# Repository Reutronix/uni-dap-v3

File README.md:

# UniDAP

**Galvanically isolated CMSIS-DAP debug probe with USB-to-I²C/SPI/GPIO bridging.**

UniDAP is an open hardware debug/programming probe. It combines a full USB-isolated CMSIS-DAP probe (SWD + UART) with a USB-to-I²C/SPI/GPIO bridge, so a single USB-C cable gives you target programming, a serial console, general-purpose bus access, and isolated power — all on the far side of a galvanic isolation barrier.

---

## Features

- **Full galvanic isolation** between the host USB and the target — data *and* power.
- **CMSIS-DAP / DAPLink probe** on an STM32F103 (SWD + virtual UART).
- **USB-to-I²C/SPI/GPIO bridge** via a WCH CH347F, exposed on the same output header.
- **Isolated power rails** to the target: 5 V, 3.3 V, and a **software-gated** power output.
- **Two SWD interfaces**: a 2.54 mm 24-position fan-out header and a standard 1.27 mm 10-pin ARM Cortex Debug box header.
- **Optional UART level shifter** referenced to the target supply.
- **Self-programmable**: the on-board STM32 can be flashed for the first time over the CH347, with no external tools.

---

## Architecture

A single USB-C connection is isolated for both data and power, then fanned out on the isolated side to the STM32 (DAPLink) and the CH347 through a 2-port USB hub.

```mermaid
flowchart TB
    subgraph HOST["Host side (non-isolated)"]
        USBC["USB-C"]
    end

    subgraph BARRIER["Isolation barrier"]
        ADUM["ADuM4160<br/>USB isolator<br/>+ current limit / reverse-current protection"]
        SN["SN6505ADBV + transformer<br/>isolated 5 V supply"]
    end

    subgraph ISO["Isolated side"]
        HUB["CY7C65634<br/>2-port USB hub"]
        STM["STM32F103<br/>DAPLink (SWD + UART)"]
        CH["CH347F<br/>USB → I²C / SPI / GPIO"]
        H20["24-pin 2.54 mm<br/>output header"]
        H10["10-pin 1.27 mm<br/>Cortex Debug"]
    end

    USBC --> ADUM --> HUB
    USBC --> SN
    SN -. isolated 5 V .-> ISO
    HUB --> STM
    HUB --> CH
    STM -->|SWD + UART| H20
    STM -->|SWD| H10
    CH -->|I²C / SPI / GPIO| H20
```

### Key components

| Function | Part |
|---|---|
| Main MCU / debug probe | STM32F103 (running DAPLink) |
| USB → I²C / SPI / GPIO bridge | WCH CH347F |
| USB isolator | Analog Devices ADuM4160 |
| Isolated 5 V supply | TI SN6505ADBV push-pull transformer driver + transformer |
| USB hub (isolated side) | Cypress CY7C65634 (2-port) |
| Gated power output | ideal-diode switch, GPIO-controlled |
| UART level shifter (optional) | U502 (target-referenced) |

---

## Connectors & pinouts

### 24-pin 2.54 mm output header

The main fan-out header carries the SWD programming signals from the STM32, the DAPLink UART, the CH347 I²C/SPI/GPIO lines, and the isolated power rails (5 V, 3.3 V, and the gated `VOUT`). It uses an odd/even footprint: odd pins on one row, even pins on the other, with pin 1 and pin 2 side by side. Refer to on-board bottom side silkscreen.

| Pin | Signal | Group | | Pin | Signal | Group |
|----:|--------|-------|---|----:|--------|-------|
| 1 | GND | Ground | | 2 | 5V | Power |
| 3 | 3.3V | Power | | 4 | VOUT | Gated power |
| 5 | GPIO5 | GPIO | | 6 | GND | Ground |
| 7 | GND | Ground | | 8 | SCL | I²C |
| 9 | GPIO1 | GPIO | | 10 | SDA | I²C |
| 11 | SPI_SCK | SPI | | 12 | GPIO2 | GPIO |
| 13 | SPI_CS | SPI | | 14 | GND | Ground |
| 15 | SPI_MISO | SPI | | 16 | UART_TX | UART |
| 17 | SPI_MOSI | SPI | | 18 | UART_RX | UART |
| 19 | GPIO3 | GPIO | | 20 | GND | Ground |
| 21 | GND | Ground | | 22 | SWCLK | SWD |
| 23 | RESET | SWD | | 24 | SWDIO | SWD |

> **Note:** `VOUT` (pin 4) is the gated power output. In the standard configuration it is switched by CH347 **GPIO1** (pin 9) through the on-board ideal diode — see [Configuration](#configuration-jumpers--dnp-options). `RESET` (pin 23) is the target reset line.

### 10-pin 1.27 mm Cortex Debug header

Standard ARM Cortex Debug connector pinout — compatible with common SWD adapters and cables.

| Pin | Signal | Pin | Signal |
|----:|--------|----:|--------|
| 1 | VTREF | 2 | SWDIO / TMS |
| 3 | GND | 4 | SWCLK / TCK |
| 5 | GND | 6 | SWO / TDO |
| 7 | KEY (n/c) | 8 | NC / TDI |
| 9 | GNDDetect | 10 | nRESET |

### STM32 SWD programming pads (SMD)

Bare SMD pads are provided to program the STM32 over SWD directly (solder wires). Used mainly to recover a blank part or one without a USB bootloader. See [First-time STM32 programming](#first-time-stm32-programming).

---

## Configuration (jumpers & DNP options)

UniDAP ships in a **standard configuration**; several jumpers/footprints let you reconfigure it.

| Ref | Default | Function |
|---|---|---|
| **R501** | Populated | Routes CH347 **GPIO1** to the ideal-diode gate, so GPIO1 controls the **gated power output** (standard config). |
| **R502** | Unpopulated | Alternate route for CH347 GPIO1 to the main output header as a plain GPIO. **Populate R502 and remove R501** to expose GPIO1 on the header instead of driving the gated output. |
| **U502** | Unpopulated | Optional UART **level shifter**, supplied from the target voltage. |
| **R505 / R507** | Populated | Direct (unshifted) connection of the DAPLink UART to the output header. **Remove R505/R507 and populate U502** to route the UART through the level shifter. |

**Gated power output:** by default the isolated power to the target passes through an ideal-diode switch enabled by CH347 GPIO1, so power to the target can be switched under software control.

**Level-shifted UART:** in the standard configuration the DAPLink UART goes straight to the output header. Populating U502 (and removing R505/R507) shifts the UART to the target's logic level, referenced to the target supply.

---

## Firmware

The probe runs [DAPLink](https://github.com/ARMmbed/DAPLINK) (main branch).

- **Board ID:** `0080`
- **Provides:** CMSIS-DAP (SWD) + a virtual UART bridge.

### First-time STM32 programming

The STM32 can be programmed for the first time (or recovered when no USB bootloader is present) two ways:

1. **Over the CH347 (no external tools).** The CH347 UART0 is wired to the STM32 UART, and the STM32 **BOOT0** pin is driven by CH347 **GPIO0**. Asserting BOOT0 enters the STM32F103 system bootloader, and the firmware is flashed over UART. Use STM32CubeProgrammer to download the image.
2. **Over SWD.** Solder wires to the SWD SMD pads and flash with any CMSIS-DAP/ST-Link adapter.

---

## Acknowledgements

- [DAPLink](https://github.com/ARMmbed/DAPLINK) by Arm — the CMSIS-DAP firmware UniDAP is based on.
- WCH (CH347), Analog Devices (ADuM4160), TI (SN6505), Cypress/Infineon (CY7C65634).

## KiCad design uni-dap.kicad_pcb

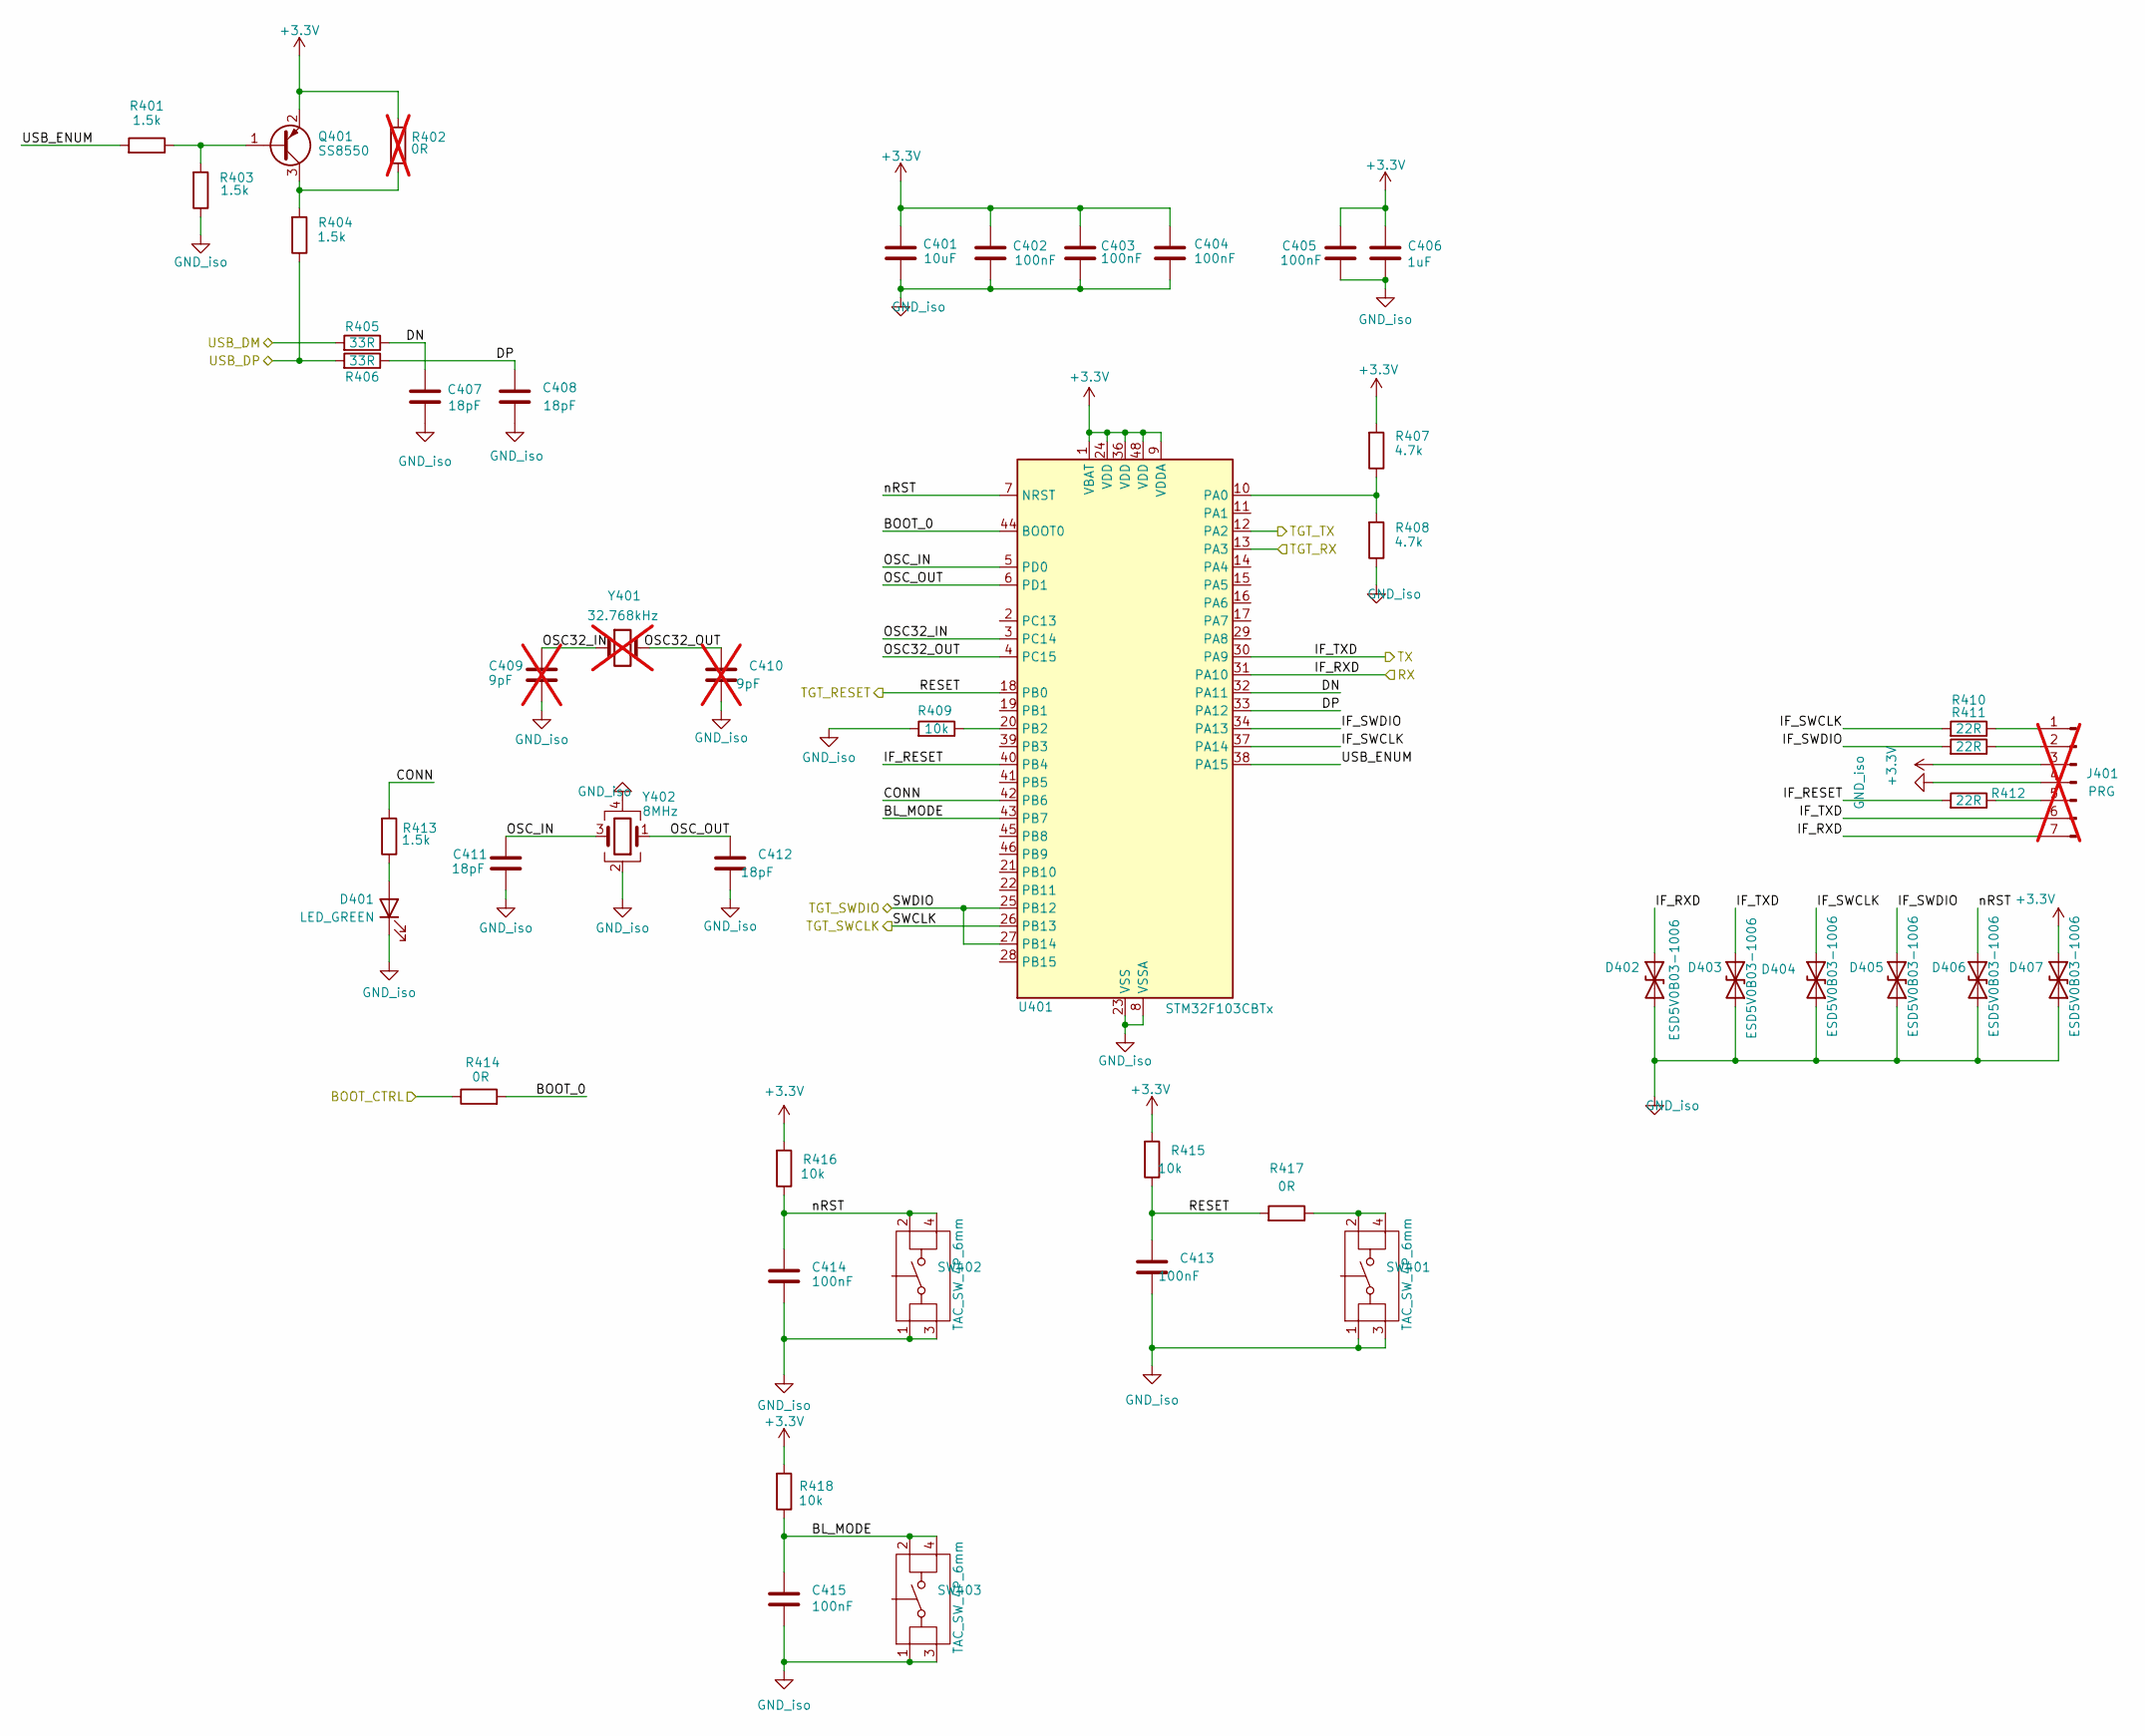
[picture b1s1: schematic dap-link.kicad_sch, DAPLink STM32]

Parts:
C401: 10uF; C_0603; Voltage 16; Manuf PN CL10A106MO8NQNC; LCSC PN C92487
C402, C403, C404, C405, C413, C414, C415: 100nF; C_0402; Voltage 16V; Manuf PN CL05B104KO5NNNC; LCSC PN C1525
C406: 1uF; C_0402; Voltage 16V; Manuf PN CL05A105KO5NNNC; LCSC PN C29266
C407, C408, C411, C412: 18pF; C_0402; Voltage 50V; Manuf PN CC0402JRNPO9BN180; LCSC PN C106202
C409, C410: 9pF; C_0402; Voltage 50V; Manuf PN CL05C090DB5NNNC; LCSC PN C111805; not fitted
D401: LED_GREEN; LED_0402; Manuf PN 16-213/GHC-YR1S1N/3T; LCSC PN C2980183
D402, D403, D404, D405, D406, D407: ESD5V0B03-1006; DFN1006-2_SMD0402; Clamping Voltage 21V; Manuf PN ESD5V0B03-1006; LCSC PN C521894
J401: PRG; PROG_HEADER_SMD; not fitted
Q401: SS8550; SOT-323_SC-70; Manuf PN SS8550WGH; LCSC PN C47355426
R401, R403, R404, R413: 1.5k; R_0402; Manuf PN RC0402FR-071K5L; LCSC PN C114759
R402: 0R; R_0402; Manuf PN RC0402FR-070RL; LCSC PN C106231; not fitted
R405, R406: 33R; R_0402; Manuf PN RC0402FR-0733RL; LCSC PN C138002
R407, R408: 4.7k; R_0402; Manuf PN RC0402FR-074K7L; LCSC PN C105871
R409, R415, R416, R418: 10k; R_0402; Manuf PN RC0402FR-0710KL; LCSC PN C60490
R410, R411, R412: 22R; R_0402; Manuf PN RC0402FR-0722RL; LCSC PN C114765
R414, R417: 0R; R_0402; Manuf PN RC0402FR-070RL; LCSC PN C106231
SW401, SW402, SW403: TAC_SW_4P_6mm; TS_6x6mm; Manuf PN TS-1002S-07026C; LCSC PN C455114
U401: STM32F103CBTx; LQFP-48_7x7mm_P0.5mm
Y401: 32.768kHz; Crystal_SMD_3215-2Pin_3.2x1.5mm; Manuf PN 9HT10-32.768KBZC-T; LCSC PN C99010; not fitted
Y402: 8MHz; Crystal_SMD_2520-4Pin_2.5x2.0mm; Manuf PN XOS25008000LT00351005; LCSC PN C37635403

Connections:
+3.3V: C401.2, C402.1, C403.1, C404.1, C405.1, C406.1, D407.2 (A2), J401.3, Q401.2 (E), R402.1, R407.1, R415.1, R416.1, R418.1, U401.1 (VBAT), U401.9 (VDDA), U401.24 (VDD), U401.36 (VDD), U401.48 (VDD); also elsewhere on the board
/DAPLink/BL_MODE: C415.1, R418.2, SW403.2 (B), SW403.4 (B), U401.43 (PB7)
/DAPLink/BOOT_0: R414.1, U401.44 (BOOT0)
/DAPLink/BOOT_CTRL: R414.2; also elsewhere on the board
/DAPLink/CONN: R413.1, U401.42 (PB6)
/DAPLink/DN: C407.1, R405.2, U401.32 (PA11)
/DAPLink/DP: C408.1, R406.2, U401.33 (PA12)
/DAPLink/IF_RESET: R412.1, U401.40 (PB4)
/DAPLink/IF_RXD: D402.2 (A2), J401.7, U401.31 (PA10); also elsewhere on the board
/DAPLink/IF_SWCLK: D404.2 (A2), R410.1, U401.37 (PA14)
/DAPLink/IF_SWDIO: D405.2 (A2), R411.1, U401.34 (PA13)
/DAPLink/IF_TXD: D403.2 (A2), J401.6, U401.30 (PA9); also elsewhere on the board
/DAPLink/OSC32_IN: C409.1, U401.3 (PC14), Y401.1
/DAPLink/OSC32_OUT: C410.1, U401.4 (PC15), Y401.2
/DAPLink/OSC_IN: C411.1, U401.5 (PD0), Y402.3
/DAPLink/OSC_OUT: C412.1, U401.6 (PD1), Y402.1
/DAPLink/RESET: C413.1, R415.2, R417.1, U401.18 (PB0); also elsewhere on the board
/DAPLink/SWCLK: U401.26 (PB13); also elsewhere on the board
/DAPLink/SWDIO: U401.25 (PB12), U401.27 (PB14); also elsewhere on the board
/DAPLink/TGT_RX: U401.13 (PA3); also elsewhere on the board
/DAPLink/TGT_TX: U401.12 (PA2); also elsewhere on the board
/DAPLink/USB_ENUM: R401.1, U401.38 (PA15)
/DAPLink/nRST: C414.1, D406.2 (A2), R416.2, SW402.2 (B), SW402.4 (B), U401.7 (NRST)
/USB/USB1_N: R405.1; also elsewhere on the board
/USB/USB1_P: R404.2, R406.1; also elsewhere on the board
GND_iso: C401.1, C402.2, C403.2, C404.2, C405.2, C406.2, C407.2, C408.2, C409.2, C410.2, C411.2, C412.2, C413.2, C414.2, C415.2, D401.1 (K), D402.1 (A1), D403.1 (A1), D404.1 (A1), D405.1 (A1), D406.1 (A1), D407.1 (A1), J401.4, R403.2, R408.2, R409.1, SW401.1 (A), SW401.3 (A), SW402.1 (A), SW402.3 (A), SW403.1 (A), SW403.3 (A), U401.8 (VSSA), U401.23 (VSS), U401.35 (VSS), U401.47 (VSS), Y402.2, Y402.4; also elsewhere on the board
unnamed: D401.2 (A), R413.2
unnamed: J401.1, R410.2
unnamed: J401.2, R411.2
unnamed: J401.5, R412.2
unnamed: Q401.1 (B), R401.2, R403.1
unnamed: Q401.3 (C), R402.2, R404.1
unnamed: R417.2, SW401.2 (B), SW401.4 (B)
unnamed: R407.2, R408.1, U401.10 (PA0)
unnamed: R409.2, U401.20 (PB2)

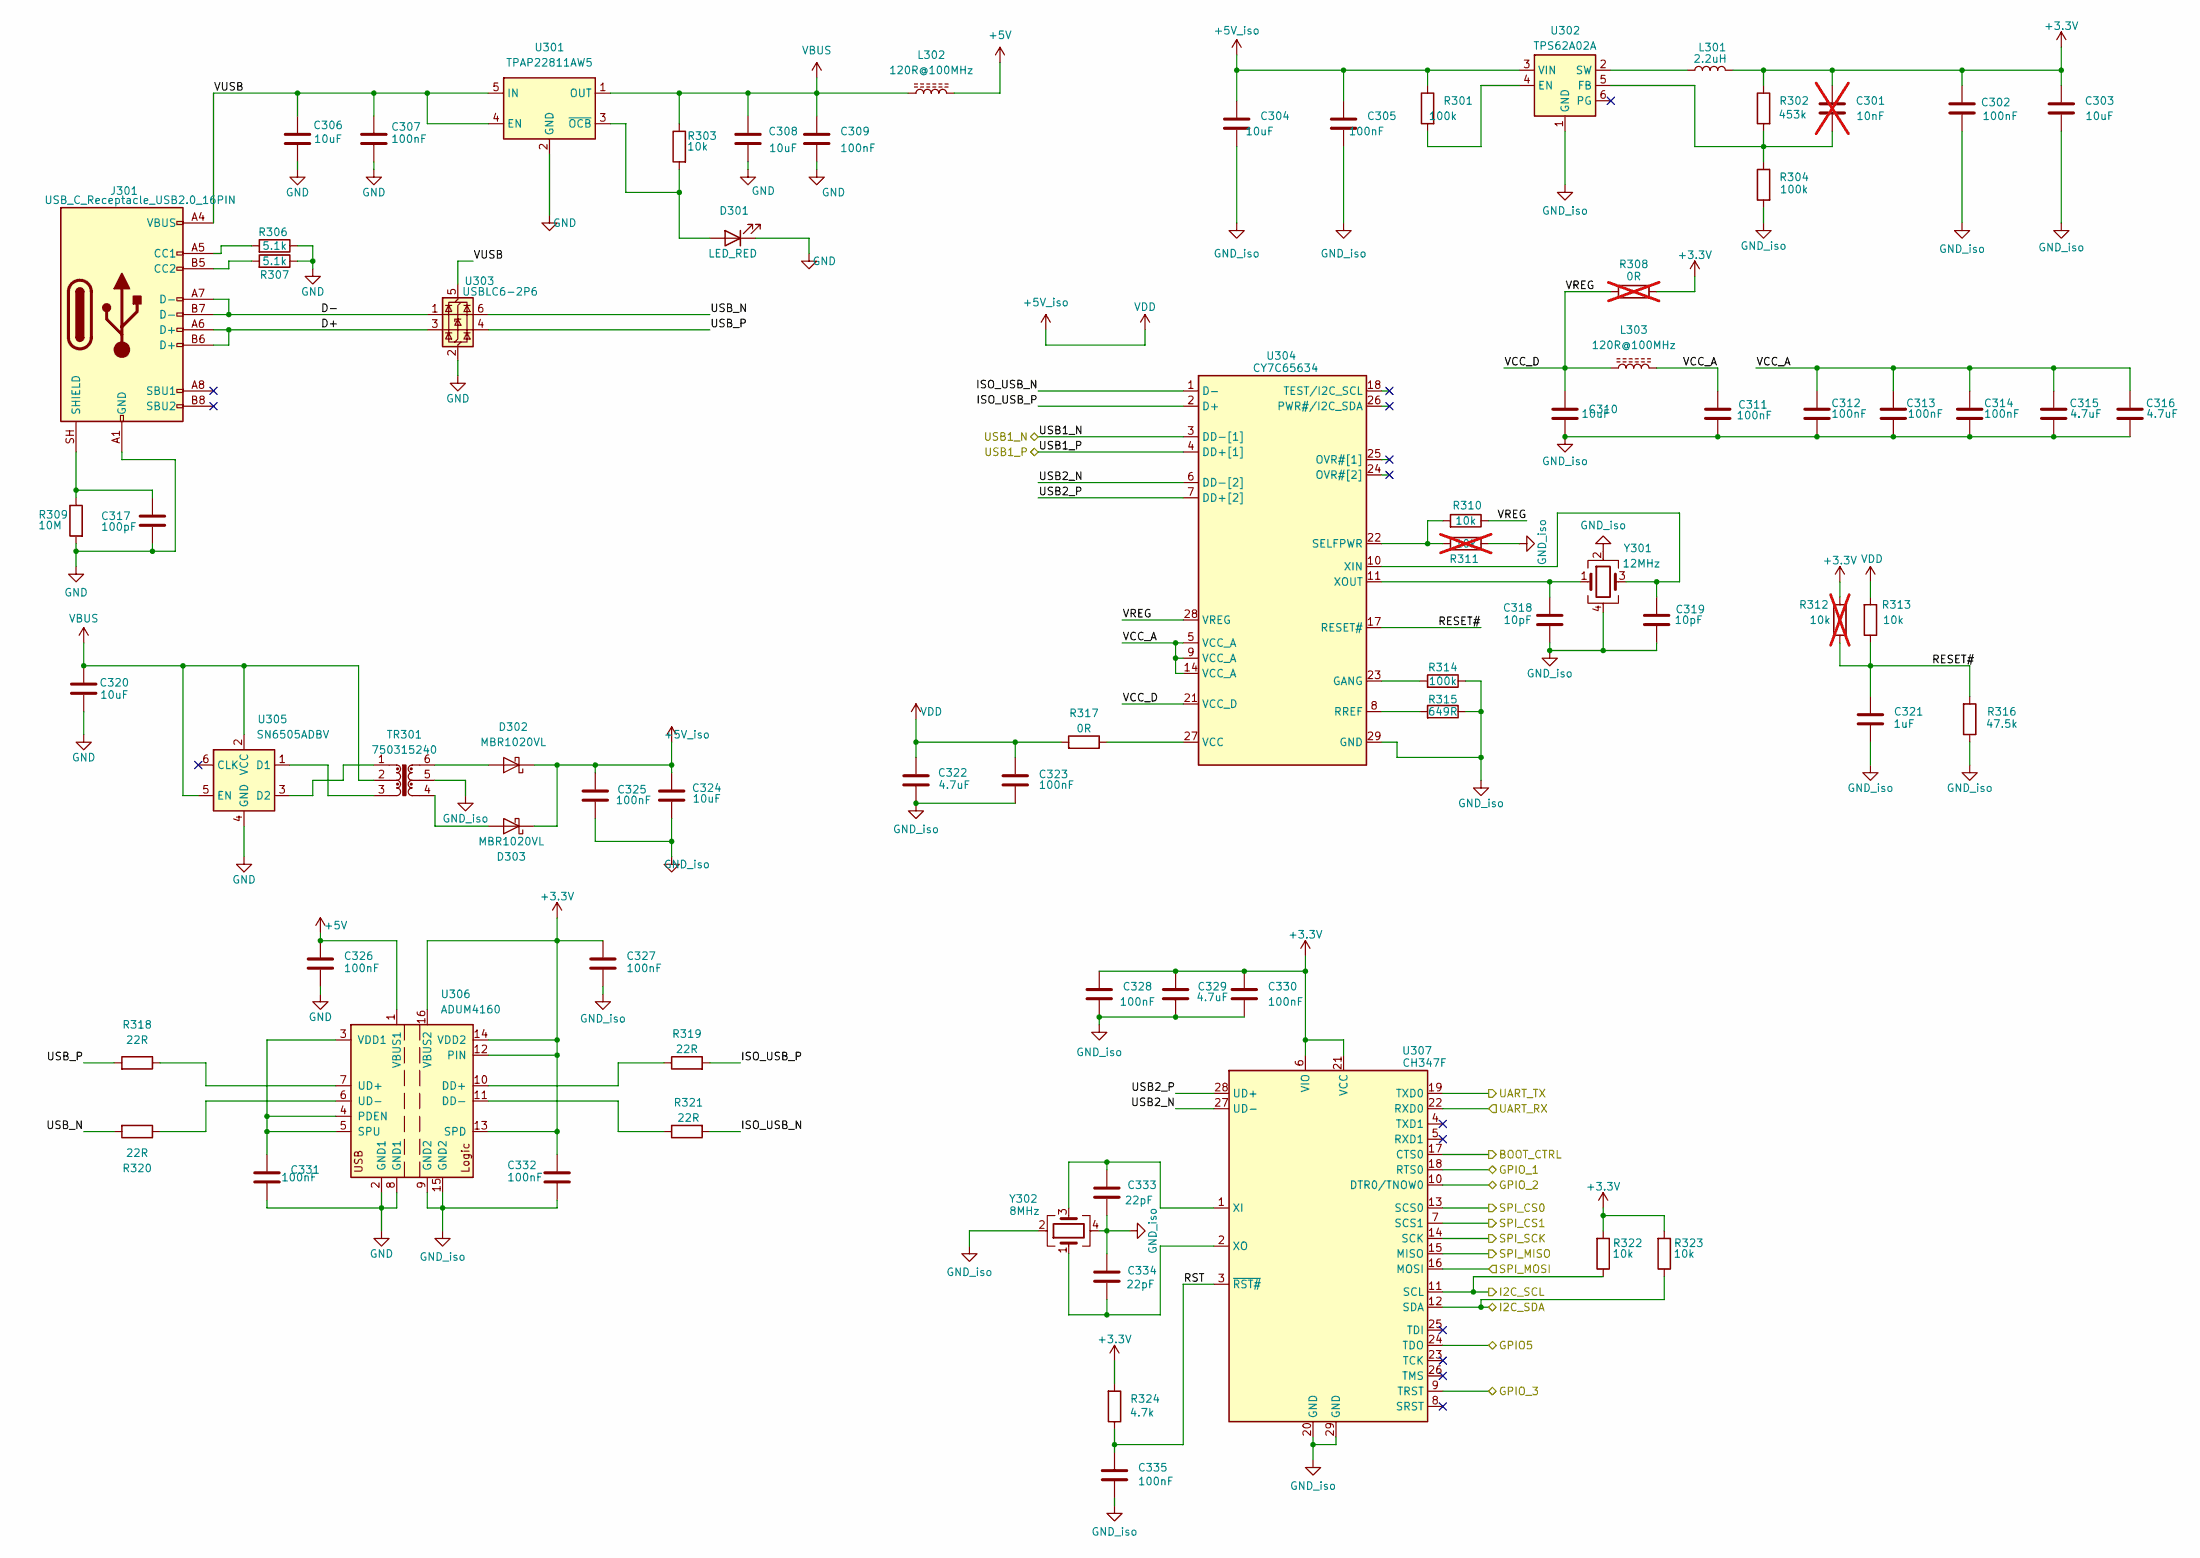
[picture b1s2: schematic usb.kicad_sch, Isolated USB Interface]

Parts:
C301: 10nF; C_0402; Voltage 50V; Manuf PN CL05B103KB5NNNC; LCSC PN C15195; not fitted
C302, C305, C307, C309, C311, C312, C313, C314, C323, C325, C326, C327, C328, C330, C331, C332, C335: 100nF; C_0402; Voltage 16V; Manuf PN CL05B104KO5NNNC; LCSC PN C1525
C303, C304, C306, C308, C310, C320, C324: 10uF; C_0603; Voltage 16; Manuf PN CL10A106MO8NQNC; LCSC PN C92487
C315, C316, C322, C329: 4.7uF; C_0402; Voltage 16; Manuf PN CL05A475MO5NUNC; LCSC PN C318563
C317: 100pF; C_0402; Voltage 50V; Manuf PN CL05C101JB5NNNC; LCSC PN C26409
C318, C319: 10pF; C_0402; Voltage 50V; Manuf PN CL05C100FB51PNC; LCSC PN C472444
C321: 1uF; C_0402; Voltage 16V; Manuf PN CL05A105KO5NNNC; LCSC PN C29266
C333, C334: 22pF; C_0402; Voltage 50V; Manuf PN CL05C220JB5NNNC; LCSC PN C70464
D301: LED_RED; LED_0402; Manuf PN 16-213/R6C-AQ2R2B/3T; LCSC PN C264407
D302, D303: MBR1020VL; D_SOD-123F; Manuf PN MBR1020VL_R1_00001; LCSC PN C391533
J301: USB_C_Receptacle_USB2.0_16PIN; USB_C_Receptacle_GCT_USB4105-xx-A_16P_TopMnt_Horizontal; Manuf PN TYPE-C 16PIN 2MD(073); LCSC PN C2765186
L301: 2.2uH; L_1008_2520Metric; Manuf PN MLP2520H2R2MT0S1; LCSC PN C383382
L302, L303: 120R@100MHz; L_0805_2012Metric; Manuf PN BLM21AG121SN1D; LCSC PN C88990
R301, R304, R314: 100k; R_0402; Manuf PN RC0402JR-07100KL; LCSC PN C106234
R302: 453k; R_0402; Manuf PN RC0402FR-07453KL; LCSC PN C137978
R303, R310, R313, R322, R323: 10k; R_0402; Manuf PN RC0402FR-0710KL; LCSC PN C60490
R306, R307: 5.1k; R_0402; Manuf PN RC0402FR-075K1L; LCSC PN C105872
R308: 0R; R_0402; Manuf PN RC0402FR-070RL; LCSC PN C106231; not fitted
R309: 10M; R_0402; Manuf PN RC0402FR-0710ML; LCSC PN C138067
R311, R312: 10k; R_0402; Manuf PN RC0402FR-0710KL; LCSC PN C60490; not fitted
R315: 649R; R_0402; Manuf PN AC0402FR-07649RL; LCSC PN C227180
R316: 47.5k; R_0402; Manuf PN RC0402FR-0747K5L; LCSC PN C137974
R317: 0R; R_0402; Manuf PN RC0402FR-070RL; LCSC PN C106231
R318, R319, R320, R321: 22R; R_0402; Manuf PN RC0402FR-0722RL; LCSC PN C114765
R324: 4.7k; R_0402; Manuf PN RC0402FR-074K7L; LCSC PN C105871
TR301: 750315240; Manuf PN 750315240
U301: ТРАР22811AW5; SOT-23-5; Manuf PN ТРАР22811AW5; LCSC PN C23380905
U302: TPS62A02A; SOT-563; Manuf PN TPS62A02ADRLR; LCSC PN C5820994
U303: USBLC6-2P6; SOT-666
U304: CY7C65634; QFN-28-1EP_5x5mm_P0.5mm_EP3.35x3.35mm; Manuf PN CY7C65634-28LTXCT; LCSC PN C2951393
U305: SN6505ADBV; SOT-23-6; Manuf PN SN6505ADBVT; LCSC PN C2650143
U306: ADUM4160; SOIC-16W_7.5x10.3mm_P1.27mm; Manuf PN ADUM4160BRWZ-RL; LCSC PN C57791
U307: CH347F; QFN-28-1EP_4x4mm_P0.4mm_EP2.3x2.3mm; Manuf PN CH347F; LCSC PN C18221627
Y301: 12MHz; Crystal_SMD_2520-4Pin_2.5x2.0mm; Manuf PN ABM10AIG-12.000MHZ-4Z-T3; LCSC PN C1985574
Y302: 8MHz; Crystal_SMD_2520-4Pin_2.5x2.0mm; Manuf PN XOS25008000LT00351005; LCSC PN C37635403

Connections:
+3.3V: C301.1, C302.1, C303.1, C327.1, C328.1, C329.1, C330.1, C332.1, L301.2, R302.2, R308.2, R312.1, R322.1, R323.1, R324.1, U306.12 (PIN), U306.13 (SPD), U306.14 (VDD2), U306.16 (VBUS2), U307.6 (VIO), U307.21 (VCC); also elsewhere on the board
+5V: C326.1, L302.2, U306.1 (VBUS1)
+5V_iso: C304.1, C305.1, C322.1, C323.1, C324.2, C325.1, D302.1 (K), D303.1 (K), R301.2, R313.1, R317.1, U302.3 (VIN); also elsewhere on the board
/DAPLink/BOOT_CTRL: U307.17 (CTS0); also elsewhere on the board
/DAPLink/IF_RXD: U307.19 (TXD0); also elsewhere on the board
/DAPLink/IF_TXD: U307.22 (RXD0); also elsewhere on the board
/Outputs/CS_OUT: U307.13 (SCS0); also elsewhere on the board
/Outputs/GPIO1_OUT: U307.18 (RTS0); also elsewhere on the board
/Outputs/GPIO2_OUT: U307.10 (DTR0/TNOW0); also elsewhere on the board
/Outputs/GPIO3_OUT: U307.9 (TRST); also elsewhere on the board
/Outputs/MISO_OUT: U307.16 (MOSI); also elsewhere on the board
/Outputs/MOSI_OUT: U307.15 (MISO); also elsewhere on the board
/Outputs/SCK_OUT: U307.14 (SCK); also elsewhere on the board
/Outputs/SCL_OUT: R322.2, U307.11 (SCL); also elsewhere on the board
/Outputs/SDA_OUT: R323.2, U307.12 (SDA); also elsewhere on the board
/Outputs/UART_OE: U307.24 (TDO); also elsewhere on the board
/USB/D+: J301.A6 (D+), J301.B6 (D+), U303.3 (I/O2)
/USB/D-: J301.A7 (D-), J301.B7 (D-), U303.1 (I/O1)
/USB/ISO_USB_N: R321.1, U304.1 (D-)
/USB/ISO_USB_P: R319.1, U304.2 (D+)
/USB/RESET#: C321.1, R312.2, R313.2, R316.1, U304.17 (RESET#)
/USB/RST: C335.1, R324.2, U307.3 (~RST#)
/USB/SPI_CS1: U307.7 (SCS1)
/USB/USB1_N: U304.3 (DD-[1]); also elsewhere on the board
/USB/USB1_P: U304.4 (DD+[1]); also elsewhere on the board
/USB/USB2_N: U304.6 (DD-[2]), U307.27 (UD-)
/USB/USB2_P: U304.7 (DD+[2]), U307.28 (UD+)
/USB/USB_N: R320.1, U303.6 (I/O1)
/USB/USB_P: R318.1, U303.4 (I/O2)
/USB/VCC_A: C311.1, C312.1, C313.1, C314.1, C315.1, C316.1, L303.2, U304.5 (VCC_A), U304.9 (VCC_A), U304.14 (VCC_A)
/USB/VCC_D: C310.1, L303.1, R308.1, R310.2, U304.21 (VCC_D), U304.28 (VREG)
/USB/VUSB: C306.1, C307.1, J301.A4 (VBUS), J301.A9 (VBUS), J301.B4 (VBUS), J301.B9 (VBUS), U301.4 (EN), U301.5 (IN), U303.5 (VBUS)
GND: C306.2, C307.2, C308.2, C309.2, C317.2, C320.2, C326.2, C331.2, D301.1 (K), J301.A1 (GND), J301.A12 (GND), J301.B1 (GND), J301.B12 (GND), R306.2, R307.2, R309.1, U301.2 (GND), U303.2 (GND), U305.4 (GND), U306.2 (GND1), U306.8 (GND1)
GND_iso: C302.2, C303.2, C304.2, C305.2, C310.2, C311.2, C312.2, C313.2, C314.2, C315.2, C316.2, C318.2, C319.2, C321.2, C322.2, C323.2, C324.1, C325.2, C327.2, C328.2, C329.2, C330.2, C332.2, C333.2, C334.1, C335.2, R304.1, R311.2, R314.2, R315.2, R316.2, TR301.5, U302.1 (GND), U304.29 (GND), U306.9 (GND2), U306.15 (GND2), U307.20 (GND), U307.29 (GND), Y301.2, Y301.4, Y302.2, Y302.4; also elsewhere on the board
unnamed: D301.2 (A), R303.1, U301.3 (~OCB)
unnamed: D302.2 (A), TR301.6
unnamed: D303.2 (A), TR301.4
unnamed: J301.A5 (CC1), R306.1
unnamed: J301.B5 (CC2), R307.1
unnamed: C317.1, J301.SH (SHIELD), R309.2
unnamed: R301.1, U302.4 (EN)
unnamed: C301.2, R302.1, R304.2, U302.5 (FB)
unnamed: L301.1, U302.2 (SW)
unnamed: R314.1, U304.23 (GANG)
unnamed: R315.1, U304.8 (RREF)
unnamed: R310.1, R311.1, U304.22 (SELFPWR)
unnamed: R317.2, U304.27 (VCC)
unnamed: C319.1, U304.10 (XIN), Y301.3
unnamed: C318.1, U304.11 (XOUT), Y301.1
unnamed: TR301.3, U305.1 (D1)
unnamed: TR301.1, U305.3 (D2)
unnamed: R319.2, U306.10 (DD+)
unnamed: R321.2, U306.11 (DD-)
unnamed: C331.1, U306.3 (VDD1), U306.4 (PDEN), U306.5 (SPU)
unnamed: R318.2, U306.7 (UD+)
unnamed: R320.2, U306.6 (UD-)
unnamed: C333.1, U307.1 (XI), Y302.3
unnamed: C334.2, U307.2 (XO), Y302.1
VBUS: C308.1, C309.1, C320.1, L302.1, R303.2, TR301.2, U301.1 (OUT), U305.2 (VCC), U305.5 (EN)

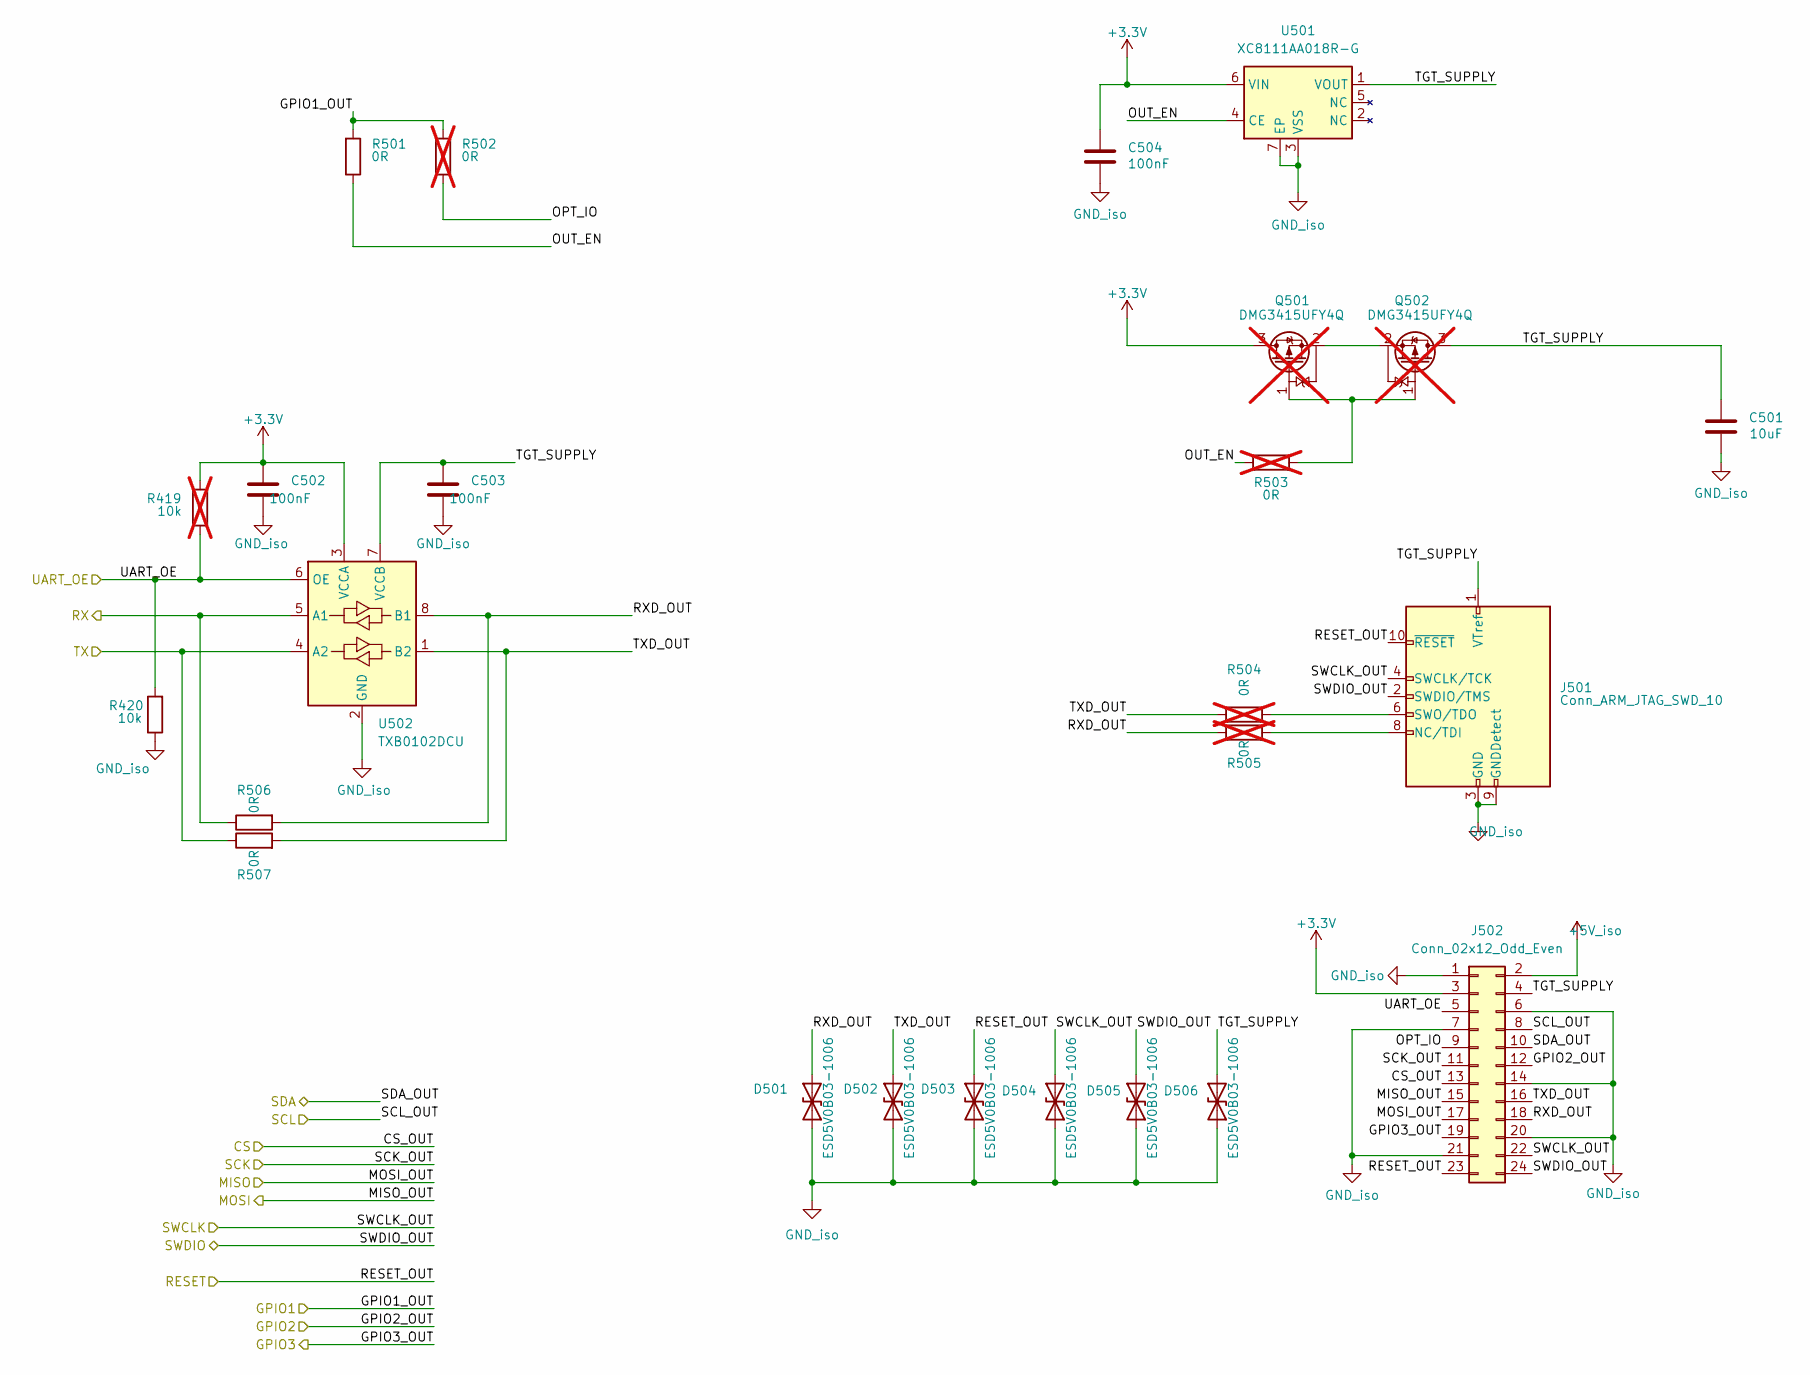
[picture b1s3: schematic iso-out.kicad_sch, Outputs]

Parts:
C501: 10uF; C_0603; Voltage 16; Manuf PN CL10A106MO8NQNC; LCSC PN C92487
C502, C503, C504: 100nF; C_0402; Voltage 16V; Manuf PN CL05B104KO5NNNC; LCSC PN C1525
D501, D502, D503, D504, D505, D506: ESD5V0B03-1006; DFN1006-2_SMD0402; Clamping Voltage 21V; Manuf PN ESD5V0B03-1006; LCSC PN C521894
J501: Conn_ARM_JTAG_SWD_10; SAMTEC_FTSH-105-XX-X-DV
J502: Conn_02x12_Odd_Even
Q501, Q502: DMG3415UFY4Q; DMG3415UFY4Q-7; Manuf PN DMG3415UFY4Q; LCSC PN C3282101; not fitted
R419: 10k; R_0402; Manuf PN RC0402FR-0710KL; LCSC PN C60490; not fitted
R420: 10k; R_0402; Manuf PN RC0402FR-0710KL; LCSC PN C60490
R501, R506, R507: 0R; R_0402; Manuf PN RC0402FR-070RL; LCSC PN C106231
R502, R503, R504, R505: 0R; R_0402; Manuf PN RC0402FR-070RL; LCSC PN C106231; not fitted
U501: XC8111AA018R-G; USP-6B06; Manuf PN XC8111AA018R-G; LCSC PN C17462394
U502: TXB0102DCU; VSSOP-8_2.3x2mm_P0.5mm; Manuf PN TXB0102DCUT; LCSC PN C2677366

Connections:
+3.3V: C502.1, C504.1, J502.3, Q501.3 (D), R419.1, U501.6 (VIN), U502.3 (VCCA); also elsewhere on the board
+5V_iso: J502.2; also elsewhere on the board
/DAPLink/RESET: D503.2 (A2), J501.10 (~RESET), J502.23; also elsewhere on the board
/DAPLink/SWCLK: D504.2 (A2), J501.4 (SWCLK/TCK), J502.22; also elsewhere on the board
/DAPLink/SWDIO: D505.2 (A2), J501.2 (SWDIO/TMS), J502.24; also elsewhere on the board
/DAPLink/TGT_RX: R506.2, U502.5 (A1); also elsewhere on the board
/DAPLink/TGT_TX: R507.2, U502.4 (A2); also elsewhere on the board
/Outputs/CS_OUT: J502.13; also elsewhere on the board
/Outputs/GPIO1_OUT: R501.1, R502.1; also elsewhere on the board
/Outputs/GPIO2_OUT: J502.12; also elsewhere on the board
/Outputs/GPIO3_OUT: J502.19; also elsewhere on the board
/Outputs/MISO_OUT: J502.15; also elsewhere on the board
/Outputs/MOSI_OUT: J502.17; also elsewhere on the board
/Outputs/OPT_IO: J502.9, R502.2
/Outputs/OUT_EN: R501.2, R503.2, U501.4 (CE)
/Outputs/RXD_OUT: D501.2 (A2), J502.18, R505.2, R506.1, U502.8 (B1)
/Outputs/SCK_OUT: J502.11; also elsewhere on the board
/Outputs/SCL_OUT: J502.8; also elsewhere on the board
/Outputs/SDA_OUT: J502.10; also elsewhere on the board
/Outputs/TGT_SUPPLY: C501.1, C503.1, D506.2 (A2), J501.1 (VTref), J502.4, Q502.3 (D), U501.1 (VOUT), U502.7 (VCCB)
/Outputs/TXD_OUT: D502.2 (A2), J502.16, R504.2, R507.1, U502.1 (B2)
/Outputs/UART_OE: J502.5, R419.2, R420.1, U502.6 (OE); also elsewhere on the board
GND_iso: C501.2, C502.2, C503.2, C504.2, D501.1 (A1), D502.1 (A1), D503.1 (A1), D504.1 (A1), D505.1 (A1), D506.1 (A1), J501.3 (GND), J501.5 (GND), J501.9 (GNDDetect), J502.1, J502.6, J502.7, J502.14, J502.20, J502.21, R420.2, U501.3 (VSS), U501.7 (EP), U502.2 (GND); also elsewhere on the board
unnamed: J501.8 (NC/TDI), R505.1
unnamed: J501.6 (SWO/TDO), R504.1
unnamed: Q501.1 (G), Q502.1 (G), R503.1
unnamed: Q501.2 (S), Q502.2 (S)

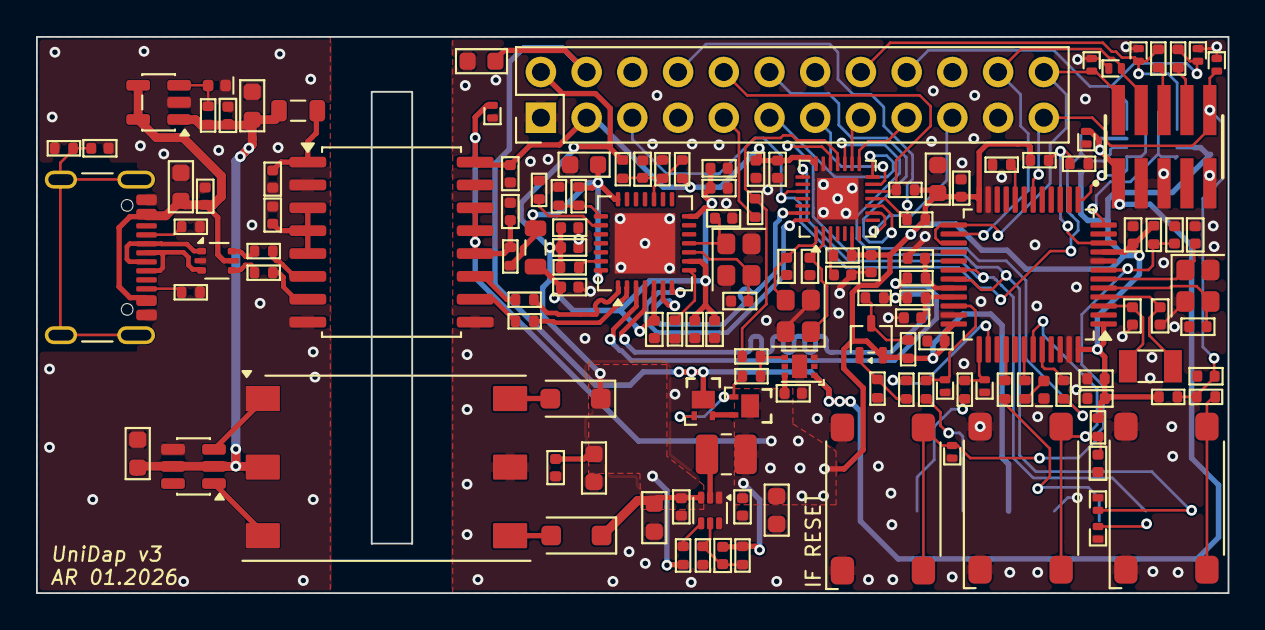
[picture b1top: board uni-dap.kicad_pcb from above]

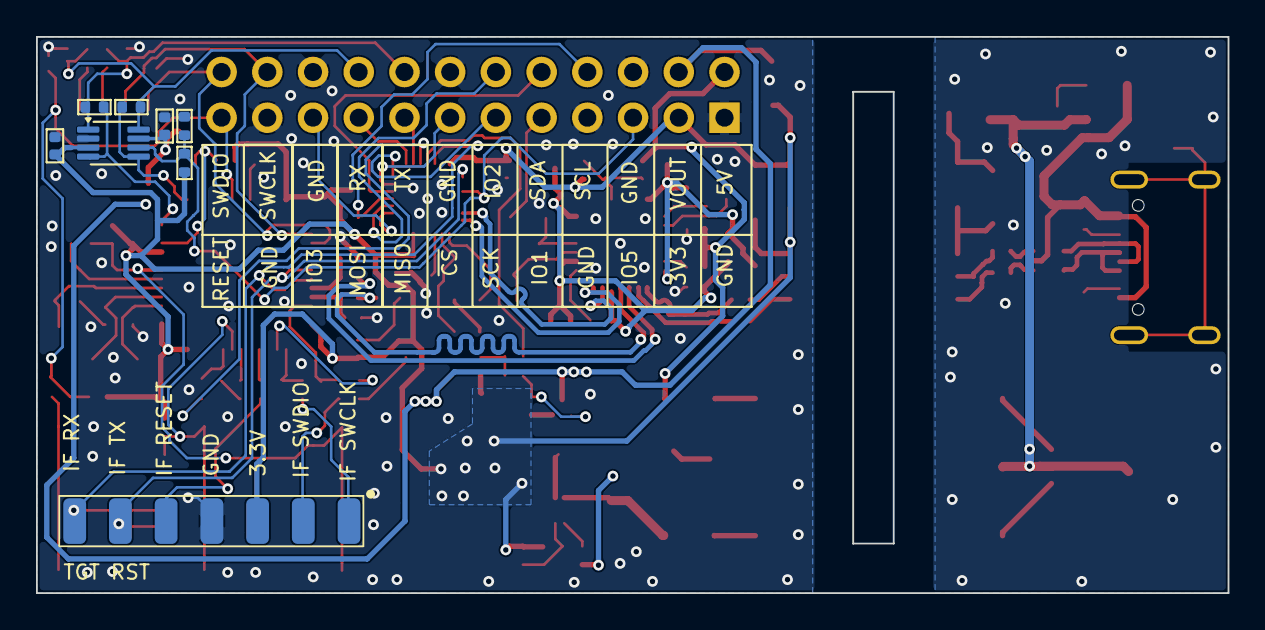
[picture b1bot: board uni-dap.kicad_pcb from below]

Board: 4 copper layers, 66.2 x 30.9 mm, 149 parts (8 on the bottom side), 95 nets.

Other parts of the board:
PCB101: PCB; 4layer_ENIG_GREEN_JLC7628

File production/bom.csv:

Designator,Footprint,Quantity,Value,LCSC Part #
"C302, C305, C307, C309, C311, C312, C313, C314, C323, C325, C326, C327, C328, C330, C331, C332, C335, C402, C403, C404, C405, C413, C414, C415, C502, C503, C504",C_0402,27,100nF,C1525
"C303, C304, C306, C308, C310, C320, C324, C401, C501",C_0603,9,10uF,C92487
"C315, C316, C322, C329",C_0402,4,4.7uF,C318563
C317,C_0402,1,100pF,C26409
"C318, C319",C_0402,2,10pF,C472444
"C321, C406",C_0402,2,1uF,C29266
"C333, C334",C_0402,2,22pF,C70464
"C407, C408, C411, C412",C_0402,4,18pF,C106202
D301,LED_0402,1,LED_RED,C264407
"D302, D303",D_SOD-123F,2,MBR1020VL,
D401,LED_0402,1,LED_GREEN,C2980183
"D402, D403, D404, D405, D406, D407, D501, D502, D503, D504, D505, D506",DFN1006-2_SMD0402,12,ESD5V0B03-1006,C521894
J301,USB_C_Receptacle_GCT_USB4105-xx-A_16P_TopMnt_Horizontal,1,USB_C_Receptacle_USB2.0_16PIN,C2765186
J501,SAMTEC_FTSH-105-XX-X-DV,1,Conn_ARM_JTAG_SWD_10,
J502,PinHeader_2x12_P2.54mm_Vertical,1,Conn_02x12_Odd_Even,
L301,1008,1,2.2uH,C383382
"L302, L303",0805,2,120R@100MHz,C88990
Q401,SOT-323_SC-70,1,SS8550,C47355426
"R301, R304, R314",R_0402,3,100k,C106234
R302,R_0402,1,453k,C137978
"R303, R310, R313, R322, R323, R409, R415, R416, R418, R420",R_0402,10,10k,C60490
"R306, R307",R_0402,2,5.1k,C105872
R309,R_0402,1,10M,C138067 
R315,R_0402,1,649R,C227180
R316,R_0402,1,47.5k,C137974
"R317, R414, R417, R501, R506, R507",R_0402,6,0R,C106231
"R318, R319, R320, R321, R410, R411, R412",R_0402,7,22R,C114765
"R324, R407, R408",R_0402,3,4.7k,C105871
"R401, R403, R404, R413",R_0402,4,1.5k,C114759
"R405, R406",R_0402,2,33R,C138002
"SW401, SW402, SW403",TS_6x6mm,3,TAC_SW_4P_6mm,C455114
TR301,750315240,1,750315240,
U301,SOT-23-5,1,ТРАР22811AW5,C23380905
U302,SOT-563,1,TPS62A02A,C5820994
U303,SOT-666,1,USBLC6-2P6,
U304,QFN-28-1EP_5x5mm_P0.5mm_EP3.35x3.35mm,1,CY7C65634,C2951393
U305,SOT-23-6,1,SN6505ADBV,C2650143
U306,SOIC-16W_7.5x10.3mm_P1.27mm,1,ADUM4160,C57791
U307,QFN-28-1EP_4x4mm_P0.4mm_EP2.3x2.3mm,1,CH347F,
U401,LQFP-48_7x7mm_P0.5mm,1,STM32F103CBTx,
U501,USP-6B06,1,XC8111AA018R-G,
U502,VSSOP-8_2.3x2mm_P0.5mm,1,TXB0102DCU,C2677366
Y301,Crystal_SMD_2520-4Pin_2.5x2.0mm,1,12MHz,C1985574
Y302,Crystal_SMD_2520-4Pin_2.5x2.0mm,1,8MHz,
Y402,Crystal_SMD_2520-4Pin_2.5x2.0mm,1,8MHz,C37635403
